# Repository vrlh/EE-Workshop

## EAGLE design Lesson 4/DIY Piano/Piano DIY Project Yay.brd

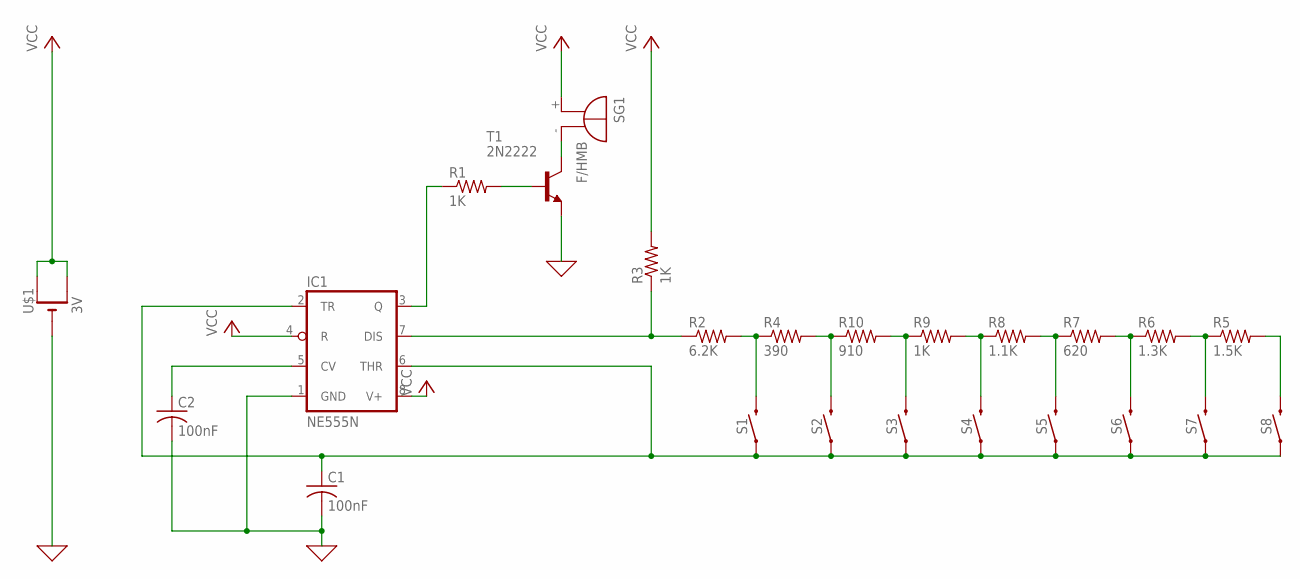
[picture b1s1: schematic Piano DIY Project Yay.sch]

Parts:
C1, C2: 100nF; C025-025X050
IC1: NE555N; DIL08
R1, R3, R9: 1K; 0207/10
R2: 6.2K; 0207/10
R4: 390; 0207/10
R5: 1.5K; 0207/10
R6: 1.3K; 0207/10
R7: 620; 0207/10
R8: 1.1K; 0207/10
R10: 910; 0207/10
S1, S2, S3, S4, S5, S6, S7, S8: MOMENTARY-SWITCH-SPST-PTH-6.0MM; TACTILE_SWITCH_PTH_6.0MM
SG1: F/HMB
T1: 2N2222; TO92
U$1: 3V; CR1220-THM

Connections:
0: C1.2, C2.2, IC1.1 (GND), T1.1 (E), U$1.-
unnamed: IC1.3 (Q), R1.1
unnamed: R1.2, T1.2 (B)
unnamed: SG1.-, T1.3 (C)
unnamed: IC1.7 (DIS), R2.1, R3.1
unnamed: R2.2, R4.1, S1.3 (2)
unnamed: R4.2, R10.1, S2.3 (2)
unnamed: R9.1, R10.2, S3.3 (2)
unnamed: R8.1, R9.2, S4.3 (2)
unnamed: R7.1, R8.2, S5.3 (2)
unnamed: R6.1, R7.2, S6.3 (2)
unnamed: R5.1, R6.2, S7.3 (2)
unnamed: R5.2, S8.3 (2)
unnamed: C1.1, IC1.2 (TR), IC1.6 (THR), S1.1, S2.1, S3.1, S4.1, S5.1, S6.1, S7.1, S8.1
unnamed: C2.1, IC1.5 (CV)
VCC: IC1.4 (R), IC1.8 (V+), R3.2, SG1.+, U$1.+1 (+), U$1.+2 (+1)

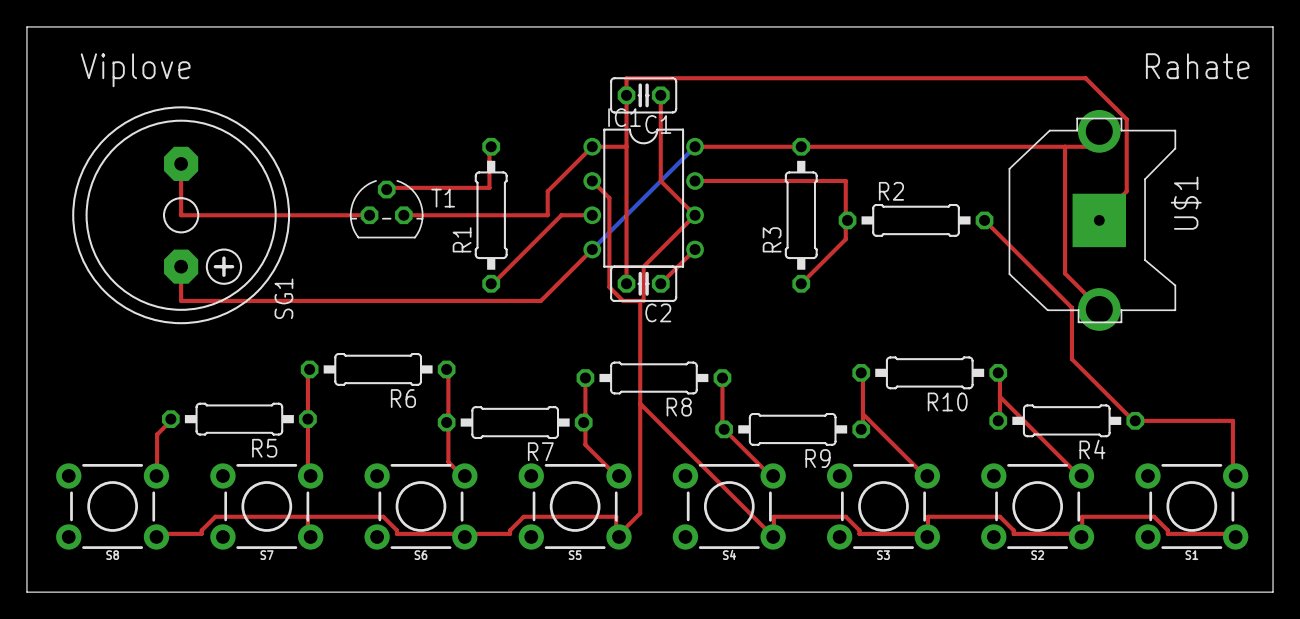
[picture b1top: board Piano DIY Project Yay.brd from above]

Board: 2 copper layers, 92.4 x 41.9 mm, 24 parts (0 on the bottom side), 16 nets.

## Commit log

2018-12-08 Accidental Blinky for DIY Piano
2018-12-16 Board

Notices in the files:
parts and their libraries:
SparkFun-Switches: Licensing: Creative Commons ShareAlike 4.0 International - https://creativecommons.org/licenses/by-sa/4.0
